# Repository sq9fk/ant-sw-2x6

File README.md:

# SP9PDF RemoteQTH Antenna Switch (6×2)

Firmware sterownika przełącznika antenowego **6 anten × 2 TRX** oparty na projekcie
[RemoteQTH 6×2 Antenna Controller](https://remoteqth.com/6x2-antenna-controler.php)
(oryginał **OK1HRA**, rev 0.3), zmodyfikowany przez **SQ9FK** na potrzeby stacji **SP9PDF**.

Urządzenie pozwala dwóm transceiverom niezależnie i bezkolizyjnie korzystać ze wspólnego
zestawu anten, z ochroną przed konfliktem, gdy oba TRX żądają tej samej anteny. Sterowanie
odbywa się ręcznie (enkoder/LCD + interfejs WWW); automatyka BCD z radia oraz blokowanie
przez PTT to funkcje **opcjonalne** (patrz [Funkcje opcjonalne](#funkcje-opcjonalne-sq9fk)),
domyślnie wyłączone.

Rozwój firmware (modyfikacje SQ9FK, dokumentacja, symulator WWW) prowadzony jest przy wsparciu
[Claude Code](https://claude.com/claude-code) (Anthropic).

## Sprzęt

- Platforma: **Arduino Nano** (ATmega328P)
- Ekspandery I/O: **MCP23017** na magistrali I²C (adresy 0x20–0x23)
- Wyświetlacz: **LCD 16×2** (jedna linia na TRX)
- Wejścia: enkoder obrotowy + podświetlany przycisk (menu ręczne)
- Pomiar napięcia zasilania na `A3` (ostrzeżenia LOW/HIGH < 10 V / > 15 V)
- Moduł Ethernet **W5500** (interfejs WWW) — w firmware **domyślnie włączony** (`#define EthModule`)

Dokumentacja sprzętowa w repo:
- Schemat (SVG): [`docs/6x2-antenna-switch-control-03-sch.svg`](docs/6x2-antenna-switch-control-03-sch.svg)
- Projekt **KiCad** rev 03 (schemat + PCB + netlista): [`hw/`](hw/)
- **Analiza połączeń** (pinout MCU, I²C, przekaźniki, BCD/PTT, OTRSP), zweryfikowana
  netlistą: [`docs/CONNECTIONS.md`](docs/CONNECTIONS.md)
- **Architektura firmware** (model stanu, pętla, serwer WWW, flagi funkcji):
  [`docs/DESIGN.md`](docs/DESIGN.md)

Źródło sprzętu: RemoteQTH / OK1HRA, licencja **CC BY-SA 4.0**
(<https://remoteqth.com/6x2-antenna-controler.php>).

## Funkcje / modyfikacje SQ9FK

W stosunku do oryginału OK1HRA (rev 0.3) wprowadzono:

- **6 anten (projekt pierwotny)** — czysty one-hot `bit0..bit5` = anteny 1..6 (bez dawnej
  7. pozycji i bez sprzężenia GXP11 4/5).
- **Radio Flex — dwa niezależne wyjścia** na `GPA7`/`GPB7` (przekaźniki `K1`/`K2`, złącza
  `J7`/`J6`), przełączane **ikonami power w wierszach TRX** (WWW), niezależne od wyboru anteny.
  Dawniej `bit7` = przekaźnik pasma GXP11 40 m.
- **Nowy wygląd WWW** wg konwencji projektu
  [`rotator_wifi_bridge`](https://github.com/sq9fk/rotator_wifi_bridge) — ciemny motyw teal, karty,
  statusy sekcji przy nagłówku „Anteny", legenda „Opis anten", zwijana karta **Settings**.
  **Responsywny (mobile-first)** — cele dotykowe min. 44×44 px poniżej 520 px, wyśrodkowana ikona
  Flex, siatka przycisków TRX zawsze wyrównana do lewej krawędzi karty niezależnie od liczby
  zawiniętych linii (etykieta TRX na własnym pełnym wierszu na wąskich ekranach). **Siatka anten
  na mobile (2026-08-02)** — wiersz zawija się deterministycznie na **4+4** (`-,1,2,3` / `4,5,6,
  power`), oba wiersze wypełniają całą szerokość karty równymi przyciskami (`flex:1 1 0`); ikona
  power już nie „ucieka" auto-marginesem na prawy kraniec, gdy zostanie sama w krótkim,
  zawiniętym wierszu (na desktopie bez zmian — nadal przy prawej krawędzi w jednym wierszu).
- **Edycja nazw przez WWW** (`WWW_EEPROM_NAMES`, karta Settings) — **nazwa stacji** (topbar) oraz
  nazwy anten 1–6, zapisywane w EEPROM (trwałe), z limitem długości 11 znaków.
- **Konfiguracja sieciowa edytowalna przez WWW** (karta Settings) — **IP, brama, maska, DNS**
  zamiast na sztywno w kodzie; zapisywane w EEPROM (`IPAddress::fromString`, walidacja — błędny
  adres jest ignorowany, stara wartość zostaje). Zmiana wymaga restartu urządzenia.
- **Awaryjna edycja sieci przez Serial (2026-08-02)** — gdy urządzenie ma źle skonfigurowane IP
  (lub bramę/maskę) i strona WWW jest nieosiągalna, IP/gateway/maska/DNS da się poprawić bez
  sieci: podłącz USB, otwórz terminal szeregowy (9600 8N1, zakończenie linii CR — w Arduino
  Serial Monitor „Both NL & CR" albo „Carriage return") i wyślij `NI=192.168.2.150`
  (analogicznie `NG=`/`NM=`/`ND=` dla bramy/maski/DNS — dokładnie ten sam format co WWW
  `/?N{I|G|M|D}={a.b.c.d}`, tylko bez `/?`). Urządzenie odpowiada `OK` albo `ERR` (błędny adres —
  stara wartość zostaje). Dostępne we wszystkich wariantach ze skonfigurowaną siecią
  (`EthModule` i/lub `OTRSP_TCP`), niezależnie od tego, czy `OTRSP` (USB) jest włączony — jeśli
  jest, komenda `N{kod}=` jest rozpoznawana przed przekazaniem reszty do parsera OTRSP, więc oba
  mechanizmy współdzielą ten sam port bez kolizji.
- **Odczyt stanu dla `rotator_wifi_bridge`** (`GET /?J` → `A=<trx1>,<trx2>`, `GET /?K` →
  `K=<nazwa1>,…,<nazwa6>,<nazwa stacji>`) — pozwala mostowi
  [`rotator_wifi_bridge`](https://github.com/sq9fk/rotator_wifi_bridge) (panel WWW rotora anteny)
  pokazać stan, **prawdziwe nazwy anten**, **nazwę samego przełącznika** i przełączać TRX1/TRX2
  z jednego miejsca, zwykłym HTTP GET (`/?S{bank}{kod}`, tak jak własny panel WWW tego urządzenia)
  — bez OTRSP, które zostaje zarezerwowane wyłącznie dla programu logującego. Oba endpointy
  reużywają istniejący nagłówek HTTP (`HTTP_HEAD`) zamiast nowego literału, koszt: **+68 B** (`/?J`),
  **+72 B** (`/?K`, 6 nazw anten) i dodatkowe **+16 B** za 7. pole (nazwa stacji) zamiast osobnego
  endpointu (patrz `docs/DESIGN.md` §7/§9) — **zapas na domyślnym wariancie to już tylko ~90 B**.
- **Sterowanie OTRSP** (SO2R, zgodne z [protokołem OTRSP](https://www.k1xm.org/OTRSP/OTRSP_Protocol.pdf))
  — komendy `AUX1`/`AUX2`, zapytania `?AUX1`/`?AUX2`/`?NAME`/`?`, zgodne m.in. z N1MM+. Komendy
  kończy CR (`\r`), zgodnie ze specyfikacją. Kanał USB (`OTRSP`, domyślnie **wyłączony**) i surowe
  gniazdo TCP (`OTRSP_TCP`, domyślny port 4534, domyślnie **włączone**) są **niezależne** — można
  włączyć jeden, drugi, albo oba naraz; sam parser komend jest wspólny
  (`OTRSP_parse(cmd, Print&)`), każdy kanał ma własny, niezależny bufor linii. Każdy z nich, oraz
  **oba naraz**, mieszczą się razem ze stroną WWW (`EthModule`) — `OTRSP` (USB) z zapasem ~1,1 KB,
  `OTRSP_TCP` (gniazdo TCP, **domyślny build**) z zapasem ~398 B, oba naraz z zapasem ~346 B
  (patrz uwaga niżej) — żadna kombinacja nie jest już blokowana.
- **Automatyka BCD i blokowanie przez PTT** — dostępne jako opcje (`BCD_INPUT`, `PTT_BLOCKING`),
  domyślnie wyłączone (patrz [Funkcje opcjonalne](#funkcje-opcjonalne-sq9fk)).
- **Watchdog** (`<avr/wdt.h>`, zawsze włączony) — jeśli `loop()` się zawiesi (na WWW, TCP OTRSP,
  USB OTRSP albo czymkolwiek innym) i nie wróci w ciągu ~8 s, urządzenie samo się resetuje.
  Włączany dopiero na końcu `setup()` (po wszystkich `delay()` przy starcie — LCD/IP splash), żeby
  nie zresetować urządzenia w trakcie rozruchu.
- **Przycisk „Restart" w Settings** — realny, programowy restart urządzenia z poziomu WWW (nie
  tylko informacja, że trzeba go ręcznie zrestartować). Wykorzystuje watchdog ze skróconym
  timeoutem (15 ms) — jedyny niezawodny sposób softwarowego resetu na AVR (czyści też peryferia,
  nie tylko licznik rozkazów, w przeciwieństwie do skoku na adres 0).
- **Ostrzeżenia napięciowe** — czerwona kropka statusu w topbarze przy napięciu poza 10–15 V oraz
  ostrzeżenie na LCD — **nieblokujące** (nie zamrażają WWW/przełączania podczas awarii). Samo
  napięcie nie jest już pokazywane liczbowo w Settings (usunięte dla oszczędności flash).
- **Zawsze static IP** — bez DHCP (usunięte z projektu, patrz niżej) — urządzenie startuje pod
  stałym adresem, ustawionym w `src/main.ino` lub edytowalnym po flashowaniu przez WWW+EEPROM
  (patrz „Konfiguracja sieciowa" wyżej), IP na LCD widoczne od razu przy starcie.
- Optymalizacja rozmiaru firmware (PROGMEM, pętle WWW) i utwardzenie serwera WWW.
- **Przegląd bezpieczeństwa/poprawności (2026-07-29)** — 6 poprawek: (1) walidacja zakresu w
  OTRSP `AUX1n`/`AUX2n` (wartości >6 wcześniej powodowały odczyt poza tablicą `antRAM[]` przy
  najbliższym odświeżeniu LCD/WWW); (2) timeout 2 s na odczyt żądania WWW (wolny/zawieszony
  klient trzymał `loop()` w nieskończonej pętli, docelowo do resetu przez watchdog); (3) `volatile`
  dla zmiennych dzielonych z ISR enkodera (`enc0Pos`, `e`, `Timeout[]`); (4) usunięcie `String` z
  `show()` (heap-alokacje co ~100 ms — przy okazji odzyskało **~660 B flash**, znacznie
  poprawiając zapas domyślnego buildu); (5) `enc2()` używa własnego parametru zamiast globalnej
  zmiennej; (6) powiększony bufor żądania WWW (56 B zamiast 48 B — mocno zakodowana 11-znakowa
  nazwa anteny mogła się wcześniej obcinać w połowie).
- **Odblokowany 6. wariant (2026-08-01)** — strona WWW + OTRSP po USB **i** po TCP jednocześnie
  (`EthModule`+`OTRSP`+`OTRSP_TCP`) była dotąd blokowana przez `#error` (brakowało ~116 B); po
  odzyskaniu flash w przeglądzie z 2026-07-29 kombinacja faktycznie się mieści (zmierzone wtedy:
  97,3%/29896 B) — `#error` usunięty, wszystkie sześć wariantów jest teraz dostępnych.
- **Nazwa stacji na LCD wyśrodkowana (2026-08-02)** — była drukowana zawsze od kolumny 0 (z boku
  dla krótszych nazw); teraz liczona jest jej długość (`siteNameLen()`) i wyliczana kolumna
  startowa dla wyśrodkowania na 16-znakowej linii.
- **Strona WWW nie zwija już Settings w trakcie edycji (2026-08-02)** — dawny
  `<meta http-equiv="refresh">` przeładowywał stronę bezwarunkowo co 10 s, więc rozwinięta karta
  Settings (`<details>`, stan tylko w DOM, nie zapisany po stronie urządzenia) zwijała się z
  powrotem, zanim dało się zapisać zmianę. Zastąpione małym inline `<script>`: strona nadal
  odświeża się co 10 s, ale **tylko gdy żaden `<details>` nie jest rozwinięty** — w przeciwnym
  razie sprawdzenie jest odraczane co 2 s, aż użytkownik zwinie Settings.
- **Biblioteka Ethernet: oficjalna `arduino-libraries/Ethernet`** (była `adafruit/Ethernet2` —
  przestarzała/nieutrzymywana). Kosztuje więcej flash niż Ethernet2 (obsługa W5100/W5200/W5500
  z auto-detekcją chipu w runtime, niewyłączalna `#define`m). **DHCP usunięte z projektu** —
  kosztowało ~3,8 KB flash, a przydatne było tylko w wariantach bez strony WWW; nie warto było
  trzymać całej ścieżki kodu dla tego jednego przypadku. Strona WWW działa zawsze na
  **static IP** (ustaw `ip`/`gateway`/`subnet` w `src/main.ino` pod docelową sieć).

Domyślne nazwy anten są w `antDefault[]`, domyślna nazwa stacji w `siteDefault` (`src/main.ino`).
Przy włączonym `WWW_EEPROM_NAMES` nazwa stacji i nazwy anten 1–6 są **edytowalne przez WWW** (karta
Settings) i zapisywane w EEPROM (patrz niżej).

## Konfiguracja (dyrektywy `#define`)

| Define          | Domyślnie | Opis                                                        |
|-----------------|-----------|---------------------------------------------------------------|
| `Inputs`        | 6         | liczba anten (stała — zmiana nie jest w pełni zaimplementowana) |
| `Ports`         | 2         | liczba par IN/OUT i linii LCD (wspiera 2–4)                  |
| `inputHigh`     | **WŁ.**   | poziom aktywny wejść (HIGH)                                  |
| `OTRSP`         | WYŁ.      | włącza sterowanie OTRSP po porcie szeregowym                |
| `OTRSP_TCP`     | **WŁ.**   | surowy TCP dla OTRSP — niezależne od `OTRSP`; domyślnie razem z `EthModule` (zapas ~398 B) |
| `OTRSP_TCP_PORT`| 4534      | port surowego TCP dla OTRSP                                  |
| `SERBAUD`       | 9600      | prędkość portu szeregowego                                   |
| `EthModule`     | **WŁ.**   | włącza moduł Ethernet + interfejs WWW (zawsze static IP, bez DHCP) |

### Funkcje opcjonalne (SQ9FK)

| Define          | Domyślnie | Opis                                                    |
|-----------------|-----------|---------------------------------------------------------|
| `WWW_EEPROM_NAMES` | **WŁ.**   | edycja nazwy stacji i nazw anten 1–6 przez WWW (karta Settings), zapis w EEPROM, limit `ANT_MAXLEN` (11 zn.) |
| `BCD_INPUT`     | WYŁ.      | automatyczny wybór anteny z BCD radia (wejścia MCP IN); wyłączony = tryb wyłącznie ręczny (WWW/enkoder), bez przełącznika Manual/BCD |
| `PTT_BLOCKING`  | WYŁ.      | odczyt PTT + blokada przełączania podczas TX + plakietka PTT; wyłączony zgodnie ze zmianą HW (gniazda PTT jako wyjścia) |

> **Wykrywanie kolizji** między TRX (blokada tej samej anteny, ≠ OFF) działa **niezależnie**
> od `PTT_BLOCKING` — pozostaje aktywne. Blokada pary 4↔5 (GXP11) z projektu OK1HRA została
> usunięta — poz. 4 i 5 to teraz w pełni niezależne anteny.
>
> **Atrybucja kolizji (2026-08-03)** — gdy dwa TRX zażądają tej samej anteny, na czerwono
> podświetla się **tylko ten TRX, który przełączył się jako drugi** (ten pierwszy, już
> ustabilizowany, zostaje bez zmian) — niezależnie od numeru TRX. Górny chip statusu (mały
> kwadrat z numerem TRX) pokazuje wtedy **„OFF"** zamiast nazwy żądanej anteny, bo dokładnie tak
> wygląda stan przekaźników (wyjście zostaje wymuszone na OFF). Żądanie zablokowanego TRX
> **nie ginie** — jeśli TRX, który zajmuje antenę, ją zwolni (przełączy się gdzie indziej albo na
> OFF), zablokowany TRX automatycznie ją przejmuje **od razu, bez ponownego klikania i bez
> odświeżania strony** (poprawka z 2026-08-04 — poprzednio przejęcie działało tylko wtedy, gdy
> zwalniający TRX miał niższy numer niż zablokowany; w drugą stronę zablokowany TRX zostawał
> zawieszony na OFF aż do ręcznego odświeżenia, mimo że antena była już fizycznie wolna).
> Naprawiono też sytuację, w której strona WWW pokazywała kolor kolizji **sprzed** dopiero co
> wykonanej zmiany (trzeba było ręcznie odświeżyć) oraz fałszywe kolizje przy **OFF+OFF**
> (dwa TRX ustawione na OFF nigdy nie kolidują).

## Struktura repozytorium

```
.
├── platformio.ini                 # konfiguracja budowania (Nano / ATmega328P)
├── src/
│   └── main.ino                   # AKTUALNY firmware SP9PDF/SQ9FK
├── reference/                     # firmware referencyjny (nie budowany)
│   ├── ant-sw-6x2-03_orig.ino     #   oryginał OK1HRA rev 0.3
│   ├── ant-sw-6x2-03.ino          #   wariant rev 03
│   └── ant-sw-6x2-04.ino          #   wariant rev 04
├── docs/
│   ├── 6x2-antenna-switch-control-03-sch.svg   # schemat (RemoteQTH rev 03)
│   ├── CONNECTIONS.md             # analiza połączeń (kod + netlista)
│   └── DESIGN.md                  # architektura firmware (model stanu, WWW, flagi)
├── hw/                            # projekt KiCad rev 03 (OK1HRA, CC BY-SA 4.0)
│   ├── 6x2-antenna-switch-control-03.zip
│   └── 6x2-antenna-switch-control-03/   # .sch, .kicad_pcb, .net, .lib, .pro
├── tools/
│   ├── websim.html                # symulator interfejsu WWW (test wyglądu bez sprzętu)
│   └── serve.py                   # launcher: wystawia symulator i otwiera przeglądarkę
├── README.md
├── CLAUDE.md                      # wskazówki dla Claude Code
└── LICENSE                        # GPLv3
```

## Kompilacja i wgranie

### PlatformIO (zalecane)

```bash
# Nano ze STARYM bootloaderem (57600):
pio run -e nanoatmega328 -t upload
# Nano z NOWYM bootloaderem (115200):
pio run -e nanoatmega328new -t upload
# Podgląd portu szeregowego (9600):
pio device monitor -b 9600
```

`Wire`/`SPI` są w rdzeniu AVR; `LiquidCrystal` i `Ethernet` PlatformIO pobiera automatycznie
z `lib_deps` w [`platformio.ini`](platformio.ini). Ethernet (`#define EthModule`/`OTRSP_TCP`
w `src/main.ino`) to oficjalna biblioteka Arduino `arduino-libraries/Ethernet` (2026-07-29:
zastąpiła przestarzałą `adafruit/Ethernet2`).

> **Domyślna konfiguracja: Ethernet WŁ. + OTRSP po TCP WŁ.** (strona WWW + gniazdo TCP dla
> OTRSP, np. dla N1MM+, port 4534 — static IP). Build zweryfikowany: `pio run -e nanoatmega328`
> → **SUCCESS**, bez ostrzeżeń (Flash **98,7%** / 30322 B — **zapas ~398 B**, RAM **55,0%** / 1127 B
> — domyślne flagi: BCD/PTT wył., nazwy WWW wł., konfiguracja sieciowa edytowalna wł. (WWW **i**
> Serial, patrz „Awaryjna edycja sieci przez Serial" wyżej), watchdog wł., endpointy `/?J`+`/?K`
> dla `rotator_wifi_bridge` wł.). Zapas znacząco się poprawił po usunięciu `String` z `show()`
> (patrz niżej) — wcześniej było ~246 B; od tego czasu zjadły go poprawki UX (siatka mobile,
> atrybucja kolizji — patrz wyżej).
> Wariant **BCD+PTT razem z Ethernetem już się nie mieści** — te opcje bez `EthModule`.
>
> ⚠️ **Oficjalna biblioteka Ethernet kosztuje więcej flash niż Ethernet2** (obsługa
> W5100/W5200/W5500 z auto-detekcją chipu w runtime — niewyłączalna `#define`m, zawsze
> skompilowana). **DHCP usunięte z projektu** — kosztowało ~3,8 KB (`Dhcp.cpp`+`EthernetUdp.cpp`),
> przydatne było tylko w wariantach bez strony WWW; urządzenie zawsze startuje na **static IP**
> (ustaw `ip`/`gateway`/`subnet` w `src/main.ino` pod docelową sieć, albo edytuj po flashowaniu
> przez WWW+EEPROM). Sama strona WWW (HTML/CSS/`BufP`) kosztuje dodatkowo ~8 KB — to ona, nie
> sam Ethernet, zajmuje większość budżetu.
>
> `OTRSP` (USB) i `OTRSP_TCP` (gniazdo TCP) są **niezależne** — każdy może być włączony osobno,
> razem albo osobno, ze stroną WWW (`EthModule`) albo bez niej. Od 2026-07-29 (po przeglądzie
> bugów i odzyskaniu ~660 B flash) **żadna kombinacja już nie jest blokowana** — dawny `#error`
> dla `EthModule`+`OTRSP`+`OTRSP_TCP` naraz (brakowało ~116 B) został usunięty, bo ta kombinacja
> faktycznie się mieści. Sześć wariantów (figury poniżej z 2026-08-03, po poprawkach siatki
> mobile i atrybucji kolizji — patrz wyżej):
> - **Strona WWW + OTRSP po surowym TCP** (**obecnie, domyślne**): `#define EthModule`,
>   `//#define OTRSP`, `#define OTRSP_TCP` → Flash **98,7%** (30322 B), RAM **55,0%** (1127 B)
>   — zapas ~398 B. Wciąż najciaśniejszy z domyślnie używanych wariantów — buduj go najpierw przy
>   każdej zmianie we współdzielonym kodzie (patrz `docs/DESIGN.md` §9/§11).
> - **Strona WWW, static IP, bez OTRSP**: `#define EthModule`, `//#define OTRSP`,
>   `//#define OTRSP_TCP` → Flash **95,7%** (29394 B), RAM **50,8%** (1041 B) — zapas ~1,3 KB,
>   bezpieczniejszy wybór jeśli OTRSP nie jest potrzebne.
> - **Strona WWW + OTRSP po USB**: `#define EthModule`, `#define OTRSP`, `//#define OTRSP_TCP`
>   → Flash **97,1%** (29822 B), RAM **50,8%** (1041 B) — zapas ~898 B
> - **Strona WWW + OTRSP po USB i po TCP jednocześnie**: `#define EthModule`, `#define OTRSP`,
>   `#define OTRSP_TCP` → Flash **98,9%** (30374 B), RAM **55,0%** (1127 B) — zapas ~346 B,
>   **najciaśniejszy ze wszystkich sześciu wariantów** (odblokowany 2026-08-01); jeśli oba kanały
>   OTRSP naraz nie są naprawdę potrzebne, wybierz jeden z dwóch wariantów wyżej — mają wyraźnie
>   więcej zapasu.
> - **OTRSP po USB** (bez strony WWW): `//#define EthModule`, `#define OTRSP`, `//#define OTRSP_TCP`
>   → Flash **33,7%** (10340 B), RAM **36,1%** (739 B) — bez konfiguracji sieciowej (brak
>   `EthModule`/`OTRSP_TCP`), więc bez komend `N{I|G|M|D}=` po Serial.
> - **OTRSP po USB + surowy TCP równolegle** (bez strony WWW): `//#define EthModule`,
>   `#define OTRSP`, `#define OTRSP_TCP` → Flash **69,7%** (21412 B), RAM **54,0%** (1106 B)

### Optymalizacje rozmiaru (zastosowane)

- `port[8][6]`, `BCDmatrixOUT` → `byte` / `PROGMEM`; `ant[]` i glify LCD → `PROGMEM`
  (odczyt: `antName()` / `pgm_read_byte` / `memcpy_P`) — **−264 B RAM**.
- Generowanie przycisków WWW (poz. 0–7) i listy anten zwinięte w pętlę, `switch` na `GET`
  uproszczony do `if` — **−1808 B Flash** (bez zmiany wygenerowanego HTML).

### Optymalizacje serwera WWW (zastosowane)

- **Buforowanie całego wyjścia (`BufP`)** — w bibliotekach Wiznet (Ethernet2 i oficjalna
  `arduino-libraries/Ethernet` — sprawdzone w obu) każde `write()` to osobny segment TCP z
  busy-waitem na `SEND_OK`, a `print(F("..."))` wysyła **znak po znaku** (setki drobnych pakietów).
  Klasa `BufP` zbiera znaki w RAM i oddaje do W5500 porcjami 128 B — cała strona idzie w kilkudziesięciu
  `send()` zamiast tysiąca, **wielokrotnie szybciej** i z krótszą blokadą `loop()`. Statyczny HTML
  (nagłówek/CSS/ikona) też przez ten bufor (`out.print`), na końcu `out.done()`.
- **Batchowany odczyt żądania** — dostępne bajty czytane jednym `client.read(buf,len)` (`recv`)
  zamiast po bajcie, koniec linii wykrywany `memchr` — mniej transakcji SPI na wejściu.
- **Walidacja żądania** (kontrola zakresu banku) — obce żądania (`/favicon.ico`, gołe `GET /`)
  nie przełączają już anten i nie piszą poza tablicą `port[]` (usunięty ukryty błąd OOB).
- Czytanie tylko pierwszej linii żądania (`GET …`) + usunięty debug `Serial.print` —
  krótsza obsługa połączenia. Wygenerowany HTML bez zmian.
- Parsowanie żądania **bez `String`** — bank/kod czytane wprost z bufora `char[16]`
  (usunięty globalny `String HTTP_req`). Brak alokacji sterty na ścieżce żądania.

### Arduino IDE

1. Skopiuj `src/main.ino` do katalogu o tej samej nazwie (`main/main.ino`) lub zmień nazwę.
2. Płytka: *Arduino Nano*, procesor *ATmega328P (Old Bootloader)* w razie potrzeby.
3. Wybierz port COM, *Upload*.

> Uwaga: instalacja biblioteki `Ethernet` (Library Manager, oficjalna Arduino) jest wymagana
> dla `EthModule`/`OTRSP_TCP`. Firmware nie używa DHCP (usunięte z projektu) ani nie wymaga
> żadnych patchy biblioteki — urządzenie startuje zawsze na static IP.

## Symulator interfejsu WWW

Podgląd wyglądu strony urządzenia bez sprzętu — odtwarza HTML/CSS generowany przez firmware.
Symuluje też **protokół OTRSP** (`OTRSP_parse()` z `src/main.ino`) — dwie niezależne, włączane
osobno checkboxami sekcje "OTRSP po USB" / "OTRSP po TCP", każda z monitorem terminala
(wysłane na niebiesko, odebrane na zielono — niezależnie od tego, kto w danym trybie jest
"komputerem", a kto "urządzeniem", patrz niżej) i przyciskami szybkich komend
(`?`, `?AUX1`, `?AUX2`, `?NAME`, `AUX101`, `AUX206`). Komendy `AUX1n`/`AUX2n` faktycznie
przełączają antenę na podglądzie WWW — obie symulacje (WWW i OTRSP) dzielą ten sam stan.

```bash
python tools/serve.py
```

Skrypt wystawia stronę lokalnie (domyślnie `http://127.0.0.1:8765/websim.html`) i otwiera ją
w przeglądarce. Można też otworzyć plik [`tools/websim.html`](tools/websim.html) bez serwera —
ale wtedy **nie działają** poniższe dwie funkcje realnego połączenia (wymagają `http://`).

**Prawdziwe połączenia OTRSP** (nie tylko symulacja w JS):
- **USB** — przycisk „Połącz z prawdziwym urządzeniem" w monitorze USB używa
  [Web Serial API](https://developer.mozilla.org/en-US/docs/Web/API/Web_Serial_API)
  (Chrome/Edge) — przeglądarka prosi o wybór **realnego portu COM** i rozmawia bezpośrednio
  z podłączonym przełącznikiem antenowym (9600 8N1, jak `SERBAUD`). Wysyłane komendy i
  odpowiedzi realnego urządzenia widać w tym samym monitorze co w trybie symulacji.
- **TCP** — przycisk „Uruchom most dla N1MM+" otwiera WebSocket do `python tools/serve.py`,
  który jednocześnie nasłuchuje na **prawdziwym porcie TCP 4534** (jak `OTRSP_TCP_PORT`).
  Prawdziwy N1MM+ (albo inny program OTRSP) może się połączyć z `127.0.0.1:4534` dokładnie
  jak z prawdziwym urządzeniem w wariancie `OTRSP_TCP` — komendy trafiają do przeglądarki przez
  most (surowa "rura" bajtów w Pythonie, `tools/serve.py`), a `OTRSP_parse()` w JS liczy
  odpowiedź i odsyła ją z powrotem tym samym mostem. W tym trybie to **symulator gra rolę
  urządzenia** (odwrotnie niż USB, gdzie to my jesteśmy "komputerem" mówiącym do sprzętu).

## Licencja

- **Firmware** (`src/`, `reference/`): **GPL v3** — patrz [`LICENSE`](LICENSE).
  Oryginał © OK1HRA, modyfikacje © SQ9FK.
- **Sprzęt** (`hw/`, schemat): **CC BY-SA 4.0** © OK1HRA / RemoteQTH.com.

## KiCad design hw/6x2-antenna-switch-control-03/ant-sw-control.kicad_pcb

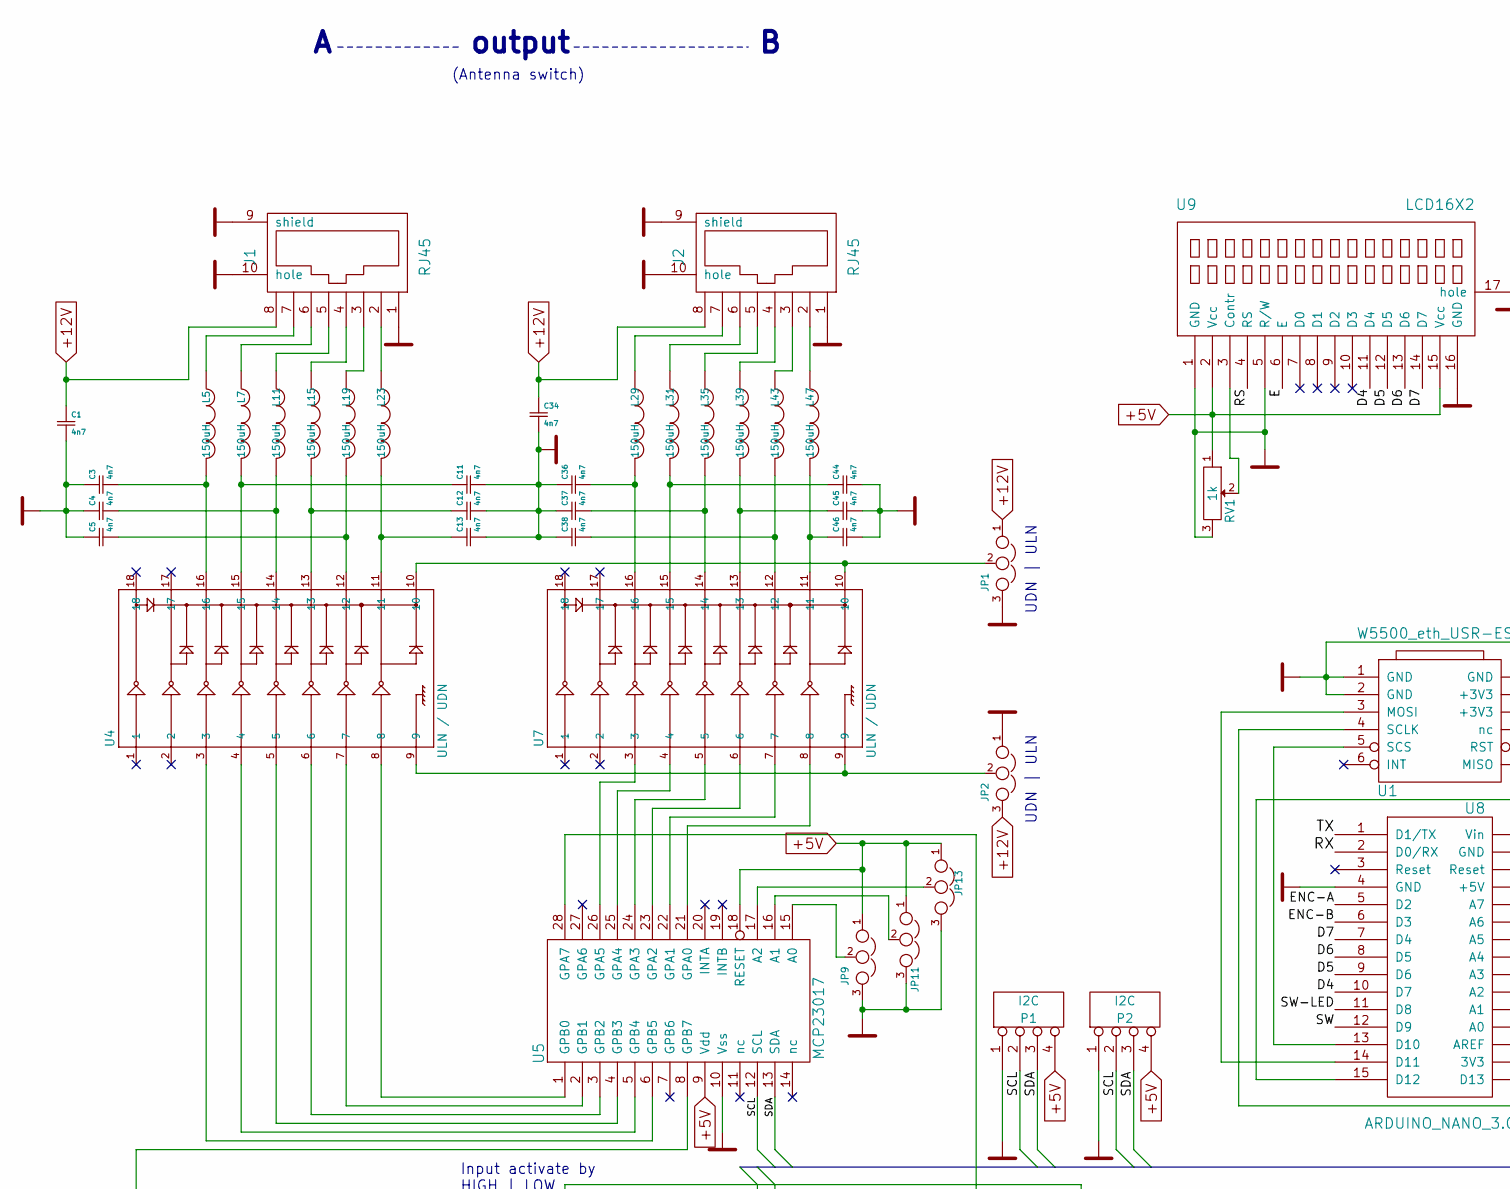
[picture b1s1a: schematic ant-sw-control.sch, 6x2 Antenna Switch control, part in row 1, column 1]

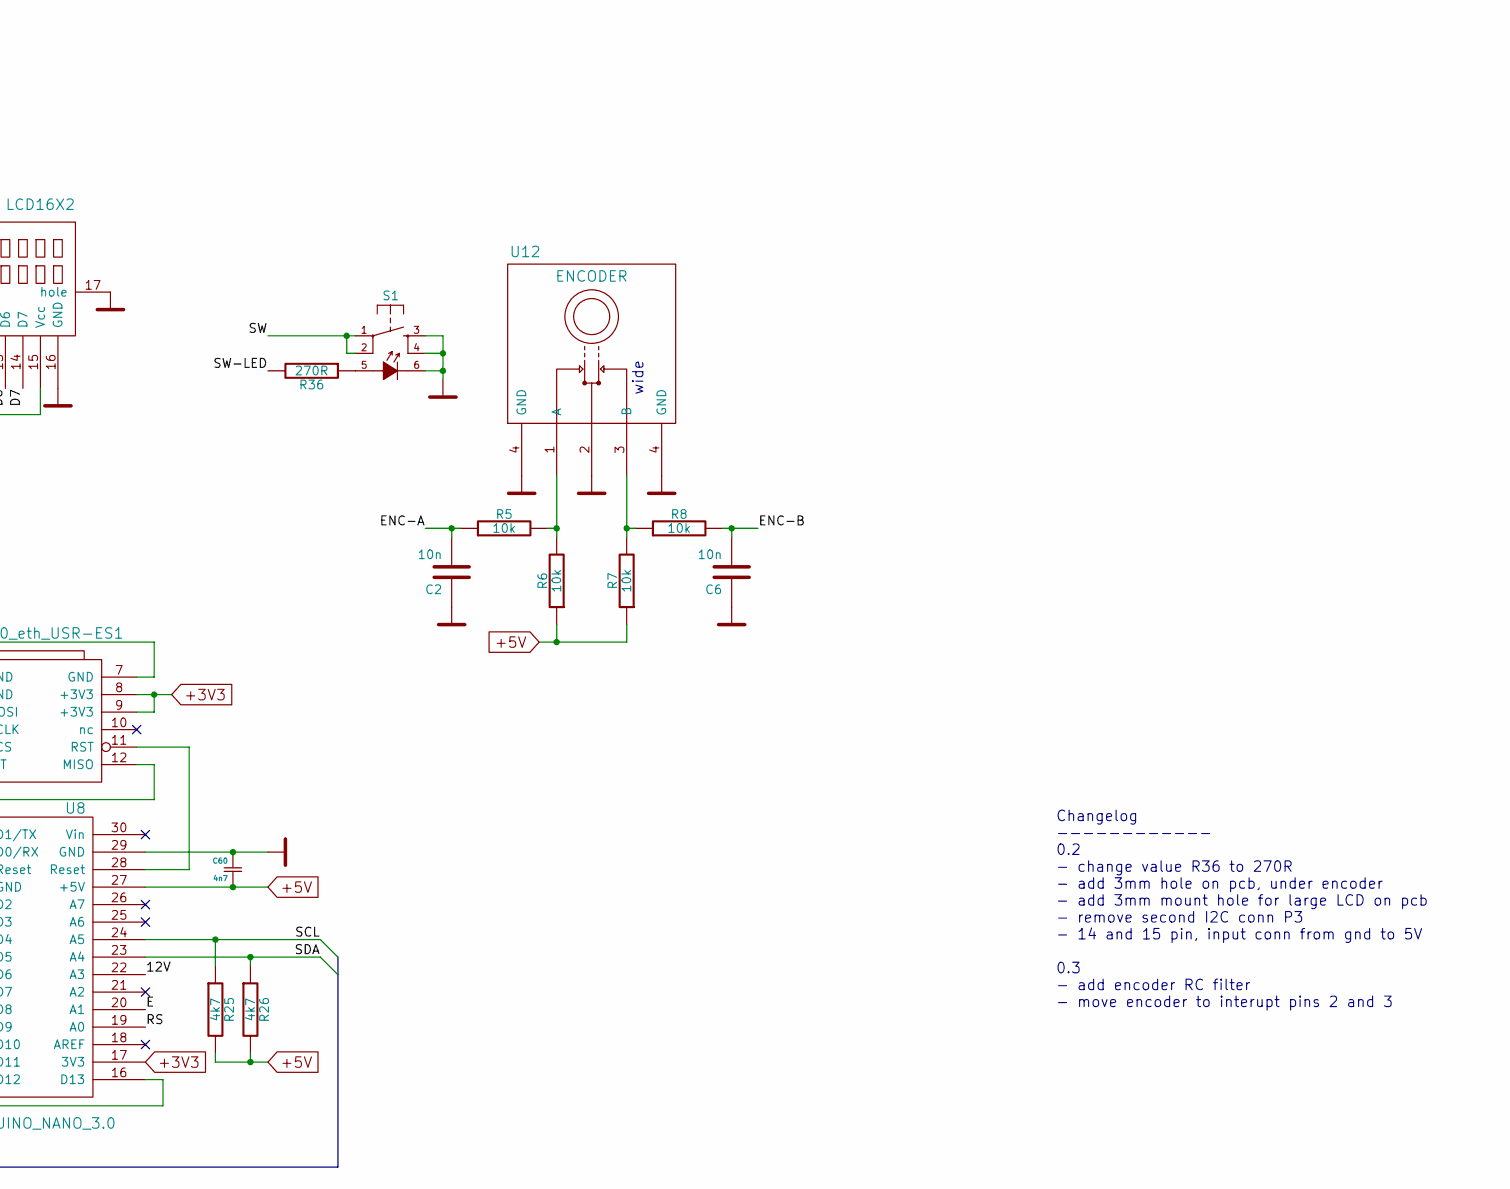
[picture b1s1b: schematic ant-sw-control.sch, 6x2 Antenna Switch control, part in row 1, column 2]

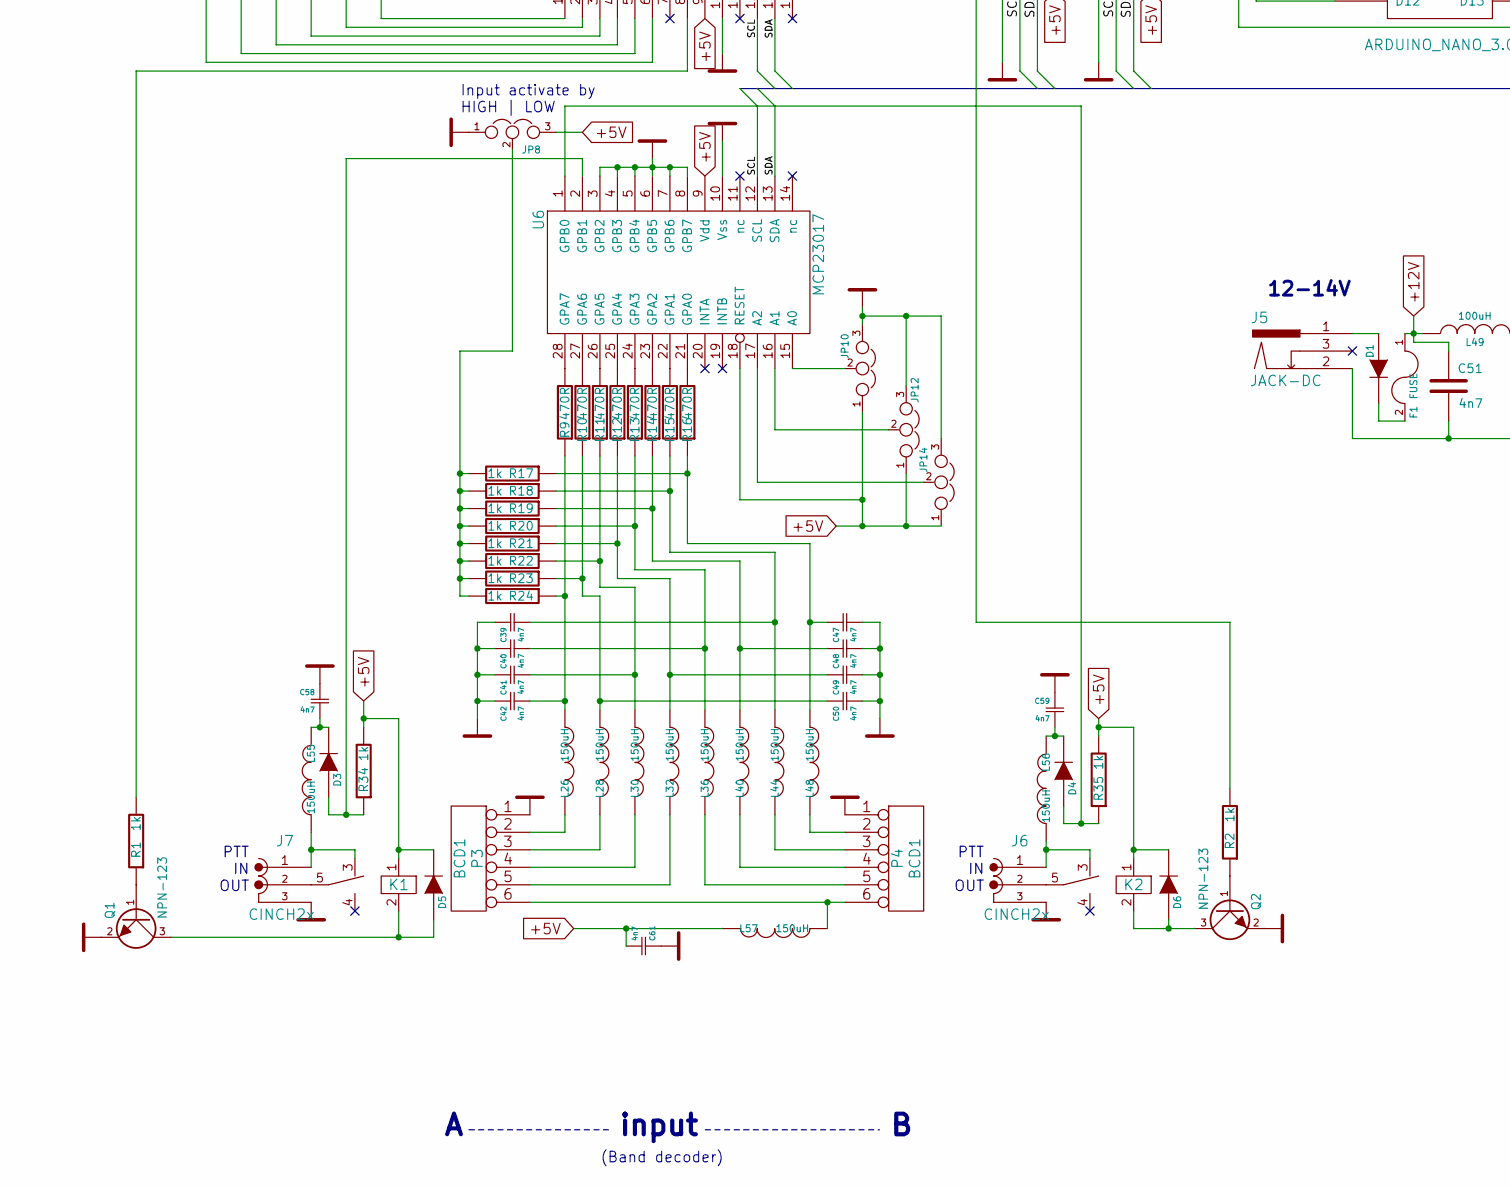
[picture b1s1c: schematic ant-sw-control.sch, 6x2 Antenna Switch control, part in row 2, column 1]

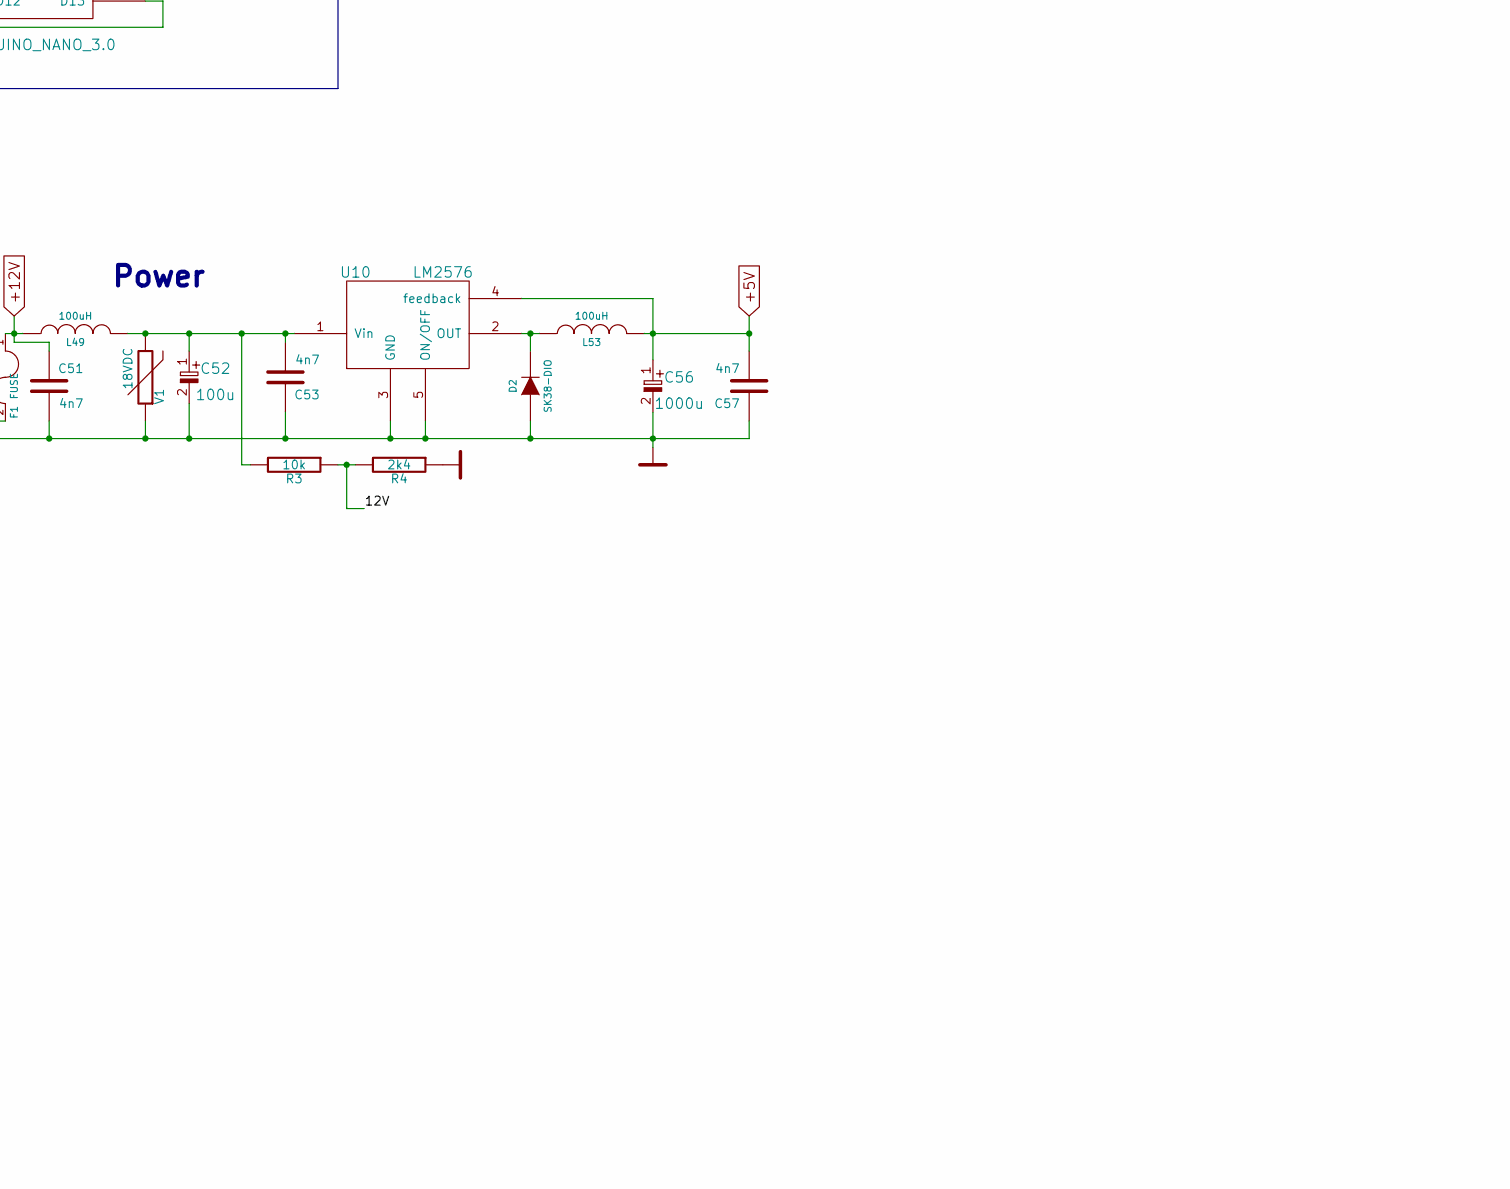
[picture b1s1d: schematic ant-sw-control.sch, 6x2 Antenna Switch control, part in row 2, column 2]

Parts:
C1, C3, C4, C5, C11, C12, C13, C34, C36, C37, C38, C39, C40, C41, C42, C44, C45, C46, C47, C48, C49, C50, C51, C53, C57, C58, C59, C60, C61: 4n7; SMD0805
C2, C6: 10n; SMD0805
C52: 100u; SMDHD-VF-6.3
C56: 1000u; SMDHD-VF
D1, D2: SK38-DIO; DO-214AB
D3, D4, D5, D6: BAS85.115; MiniMELF
F1: FUSE; SM1812
J1, J2: RJ45
J5: JACK-DC; jack-dc
J6, J7: CINCH2x; cinch-RCA-2x
JP1, JP2, JP8: JUMPER3; SIL-3
JP9, JP10, JP11, JP12, JP13, JP14: JUMPER3; SMD0805-3-jumper
K1, K2: REL-RSY
L5, L7, L11, L15, L19, L23, L26, L28, L29, L30, L31, L32, L35, L36, L39, L40, L43, L44, L47, L48, L55, L56, L57: 150uH; SM1210
L49: 100uH; L-DE0703
L53: 100uH; L-SELF-WE-PD-XXL
P1, P2: I2C; SIL-4
P3, P4: BCD1; RJ12
Q1, Q2: NPN-123; SOT23
R1, R2, R17, R18, R19, R20, R21, R22, R23, R24, R34, R35: 1k; SMD0805
R3, R5, R6, R7, R8: 10k; SMD0805
R4: 2k4; SMD0805
R9, R10, R11, R12, R13, R14, R15, R16: 470R; SMD0805
R25, R26: 4k7; SMD0805
R36: 270R; SMD0805
RV1: 1k; POT63YA
S1: KS01-BL-tact-led; tact-led-pb6156
U1: W5500_eth_USR-ES1; ETH-W5500-usr-es1
U4, U7: ULN / UDN; DIP-18
U5, U6: MCP23017; SO28
U8: ARDUINO_NANO_3.0; ArduinoNano3.0
U9: LCD16X2; LCD-16x2-vert-mount
U10: LM2576; TO-263-5
U12: ENCODER; Encoder-ED16112O-vert
V1: 18VDC; SMD0805

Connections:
+3V3: U1.8 (+3V3), U1.9 (+3V3), U8.17 (3V3)
+5V: C56.1, C57.2, C60.2, C61.2, D5.2 (K), D6.2 (K), JP8.3, JP9.1, JP10.1, JP11.1, JP12.1, JP13.1, JP14.1, K1.1, K2.1, L53.2, L57.1, P1.4, P2.4, R6.1, R7.1, R25.2, R26.2, R34.2, R35.2, RV1.1, U5.9 (Vdd), U5.18 (RESET), U6.9 (Vdd), U6.18 (RESET), U8.27 (+5V), U9.2 (Vcc), U9.15 (Vcc), U10.4 (feedback)
+12V: C1.1, C34.1, C51.1, F1.1, J1.8, J2.8, JP1.1, JP2.3, L49.1
/12V: R3.1, R4.2, U8.22 (A3)
/D4: U8.10 (D7), U9.11 (D4)
/D5: U8.9 (D6), U9.12 (D5)
/D6: U8.8 (D5), U9.13 (D6)
/D7: U8.7 (D4), U9.14 (D7)
/E: U8.20 (A1), U9.6 (E)
/ENC-A: C2.2, R5.1, U8.5 (D2)
/ENC-B: C6.2, R8.2, U8.6 (D3)
/RS: U8.19 (A0), U9.4 (RS)
/SCL: P1.2, P2.2, R25.1, U5.12 (SCL), U6.12 (SCL), U8.24 (A5)
/SDA: P1.3, P2.3, R26.1, U5.13 (SDA), U6.13 (SDA), U8.23 (A4)
/SW: S1.1, S1.2, U8.12 (D9)
/SW-LED: R36.2, U8.11 (D8)
GND: C1.2, C2.1, C3.1, C4.1, C5.1, C6.1, C11.2, C12.2, C13.2, C34.2, C36.1, C37.1, C38.1, C39.1, C40.1, C41.1, C42.1, C44.2, C45.2, C46.2, C47.2, C48.2, C49.2, C50.2, C51.2, C52.2, C53.1, C56.2, C57.1, C58.1, C59.1, C60.1, C61.1, D2.1 (A), J1.1, J1.9 (shield), J1.10 (hole), J2.1, J2.9 (shield), J2.10 (hole), J5.2, J6.3, J7.3, JP1.3, JP2.1, JP8.1, JP9.3, JP10.3, JP11.3, JP12.3, JP13.3, JP14.3, P1.1, P2.1, P3.1, P4.1, Q1.2, Q2.2, R4.1, RV1.3, S1.3, S1.4, S1.6, U1.1 (GND), U1.2 (GND), U1.7 (GND), U5.10 (Vss), U6.3 (GPB2), U6.4 (GPB3), U6.5 (GPB4), U6.6 (GPB5), U6.7 (GPB6), U6.8 (GPB7), U6.10 (Vss), U8.4 (GND), U8.29 (GND), U9.1 (GND), U9.5 (R/W), U9.16 (GND), U9.17 (hole), U10.3 (GND), U10.5 (ON/OFF), U12.2, U12.4 (GND), V1.1
unnamed: C3.2, L5.2, U4.16
unnamed: C4.2, L11.2, U4.14
unnamed: C5.2, L19.2, U4.12
unnamed: C11.1, L7.2, U4.15
unnamed: C12.1, L15.2, U4.13
unnamed: C13.1, L23.2, U4.11
unnamed: C36.2, L29.2, U7.16
unnamed: C37.2, L35.2, U7.14
unnamed: C38.2, L43.2, U7.12
unnamed: C39.2, L44.2, R15.1, R18.1
unnamed: C40.2, L36.2, R13.1, R20.1
unnamed: C41.2, L30.2, R11.1, R22.1
unnamed: C42.2, L26.2, R9.1, R24.1
unnamed: C44.1, L31.2, U7.15
unnamed: C45.1, L39.2, U7.13
unnamed: C46.1, L47.2, U7.11
unnamed: C47.1, L48.2, R16.1, R17.1
unnamed: C48.1, L40.2, R14.1, R19.1
unnamed: C49.1, L32.2, R12.1, R21.1
unnamed: C50.1, L28.2, R10.1, R23.1
unnamed: C52.1, C53.2, L49.2, R3.2, U10.1 (Vin), V1.2
unnamed: C58.2, D3.2 (K), L55.1
unnamed: C59.2, D4.2 (K), L56.1
unnamed: D1.1 (A), J5.1
unnamed: D1.2 (K), F1.2
unnamed: D2.2 (K), L53.1, U10.2 (OUT)
unnamed: D3.1 (A), R34.1, U6.2 (GPB1)
unnamed: D4.1 (A), R35.1, U6.1 (GPB0)
unnamed: D5.1 (A), K1.2, Q1.3
unnamed: D6.1 (A), K2.2, Q2.3
unnamed: J1.2, L23.1
unnamed: J1.3, L19.1
unnamed: J1.4, L15.1
unnamed: J1.5, L11.1
unnamed: J1.6, L7.1
unnamed: J1.7, L5.1
unnamed: J2.2, L47.1
unnamed: J2.3, L43.1
unnamed: J2.4, L39.1
unnamed: J2.5, L35.1
unnamed: J2.6, L31.1
unnamed: J2.7, L29.1
unnamed: J6.1, K2.3, L56.2
unnamed: J6.2, K2.5
unnamed: J7.1, K1.3, L55.2
unnamed: J7.2, K1.5
unnamed: JP1.2, U4.10, U7.10
unnamed: JP2.2, U4.9, U7.9
unnamed: JP8.2, R17.2, R18.2, R19.2, R20.2, R21.2, R22.2, R23.2, R24.2
unnamed: JP9.2, U5.15 (A0)
unnamed: JP10.2, U6.15 (A0)
unnamed: JP11.2, U5.16 (A1)
unnamed: JP12.2, U6.16 (A1)
unnamed: JP13.2, U5.17 (A2)
unnamed: JP14.2, U6.17 (A2)
unnamed: L26.1, P3.2
unnamed: L28.1, P3.3
unnamed: L30.1, P3.4
unnamed: L32.1, P3.5
unnamed: L36.1, P4.5
unnamed: L40.1, P4.4
unnamed: L44.1, P4.3
unnamed: L48.1, P4.2
unnamed: L57.2, P3.6, P4.6
unnamed: Q1.1, R1.1
unnamed: Q2.1, R2.1
unnamed: R1.2, U5.8 (GPB7)
unnamed: R2.2, U5.28 (GPA7)
unnamed: R5.2, R6.2, U12.1 (A)
unnamed: R7.2, R8.1, U12.3 (B)
unnamed: R9.2, U6.28 (GPA7)
unnamed: R10.2, U6.27 (GPA6)
unnamed: R11.2, U6.26 (GPA5)
unnamed: R12.2, U6.25 (GPA4)
unnamed: R13.2, U6.24 (GPA3)
unnamed: R14.2, U6.23 (GPA2)
unnamed: R15.2, U6.22 (GPA1)
unnamed: R16.2, U6.21 (GPA0)
unnamed: R36.1, S1.5
unnamed: RV1.2, U9.3 (Contr)
unnamed: U1.3 (MOSI), U8.14 (D11)
unnamed: U1.4 (SCLK), U8.16 (D13)
unnamed: U1.5 (SCS), U8.13 (D10)
unnamed: U1.11 (RST), U8.28 (Reset)
unnamed: U1.12 (MISO), U8.15 (D12)
unnamed: U4.3, U5.6 (GPB5)
unnamed: U4.4, U5.5 (GPB4)
unnamed: U4.5, U5.4 (GPB3)
unnamed: U4.6, U5.3 (GPB2)
unnamed: U4.7, U5.2 (GPB1)
unnamed: U4.8, U5.1 (GPB0)
unnamed: U5.21 (GPA0), U7.8
unnamed: U5.22 (GPA1), U7.7
unnamed: U5.23 (GPA2), U7.6
unnamed: U5.24 (GPA3), U7.5
unnamed: U5.25 (GPA4), U7.4
unnamed: U5.26 (GPA5), U7.3

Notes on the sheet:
12-14V
Power
output
input
Input activate by HIGH | LOW
(Band decoder)
PTT IN OUT
(Antenna switch)
Changelog ------------ 0.2 - change value R36 to 270R - add 3mm hole on pcb, under encoder - add 3mm mount hole for large LCD on pcb - remove second I2C conn P3 - 14 and 15 pin, input conn from gnd to 5V 0.3 - add encoder RC filter - move encoder to interupt pins 2 and 3
UDN | ULN
wide

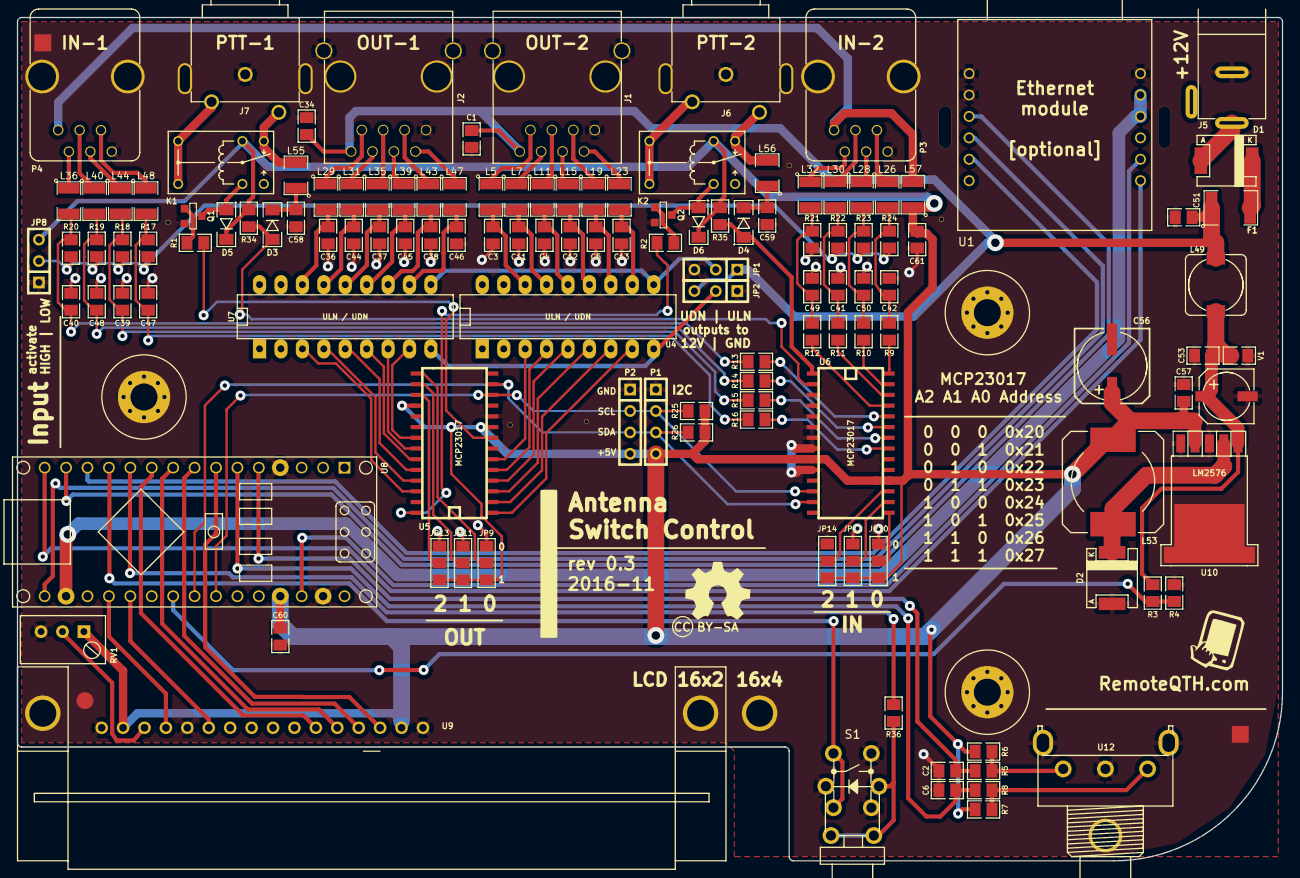
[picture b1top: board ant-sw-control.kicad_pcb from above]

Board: 2 copper layers, 150.0 x 100.0 mm, 140 parts (0 on the bottom side), 114 nets.

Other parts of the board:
Ref**: Val**; 3.2mm
Ref**#2, Ref**#3: Val**; 3.2mm
prokovka: VAL**; prokovka
prokovka#2, prokovka#3, prokovka#4, prokovka#5, prokovka#6: VAL**; prokovka-0.5
prokovka#7, prokovka#8, prokovka#9: VAL**; prokovka

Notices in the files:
hw/6x2-antenna-switch-control-03/ant-sw-control.kicad_pcb:
Licensed under the Attribution-ShareAlike 4.0 International (CC BY-SA 4.0)
http://creativecommons.org/licenses/by-sa/4.0
